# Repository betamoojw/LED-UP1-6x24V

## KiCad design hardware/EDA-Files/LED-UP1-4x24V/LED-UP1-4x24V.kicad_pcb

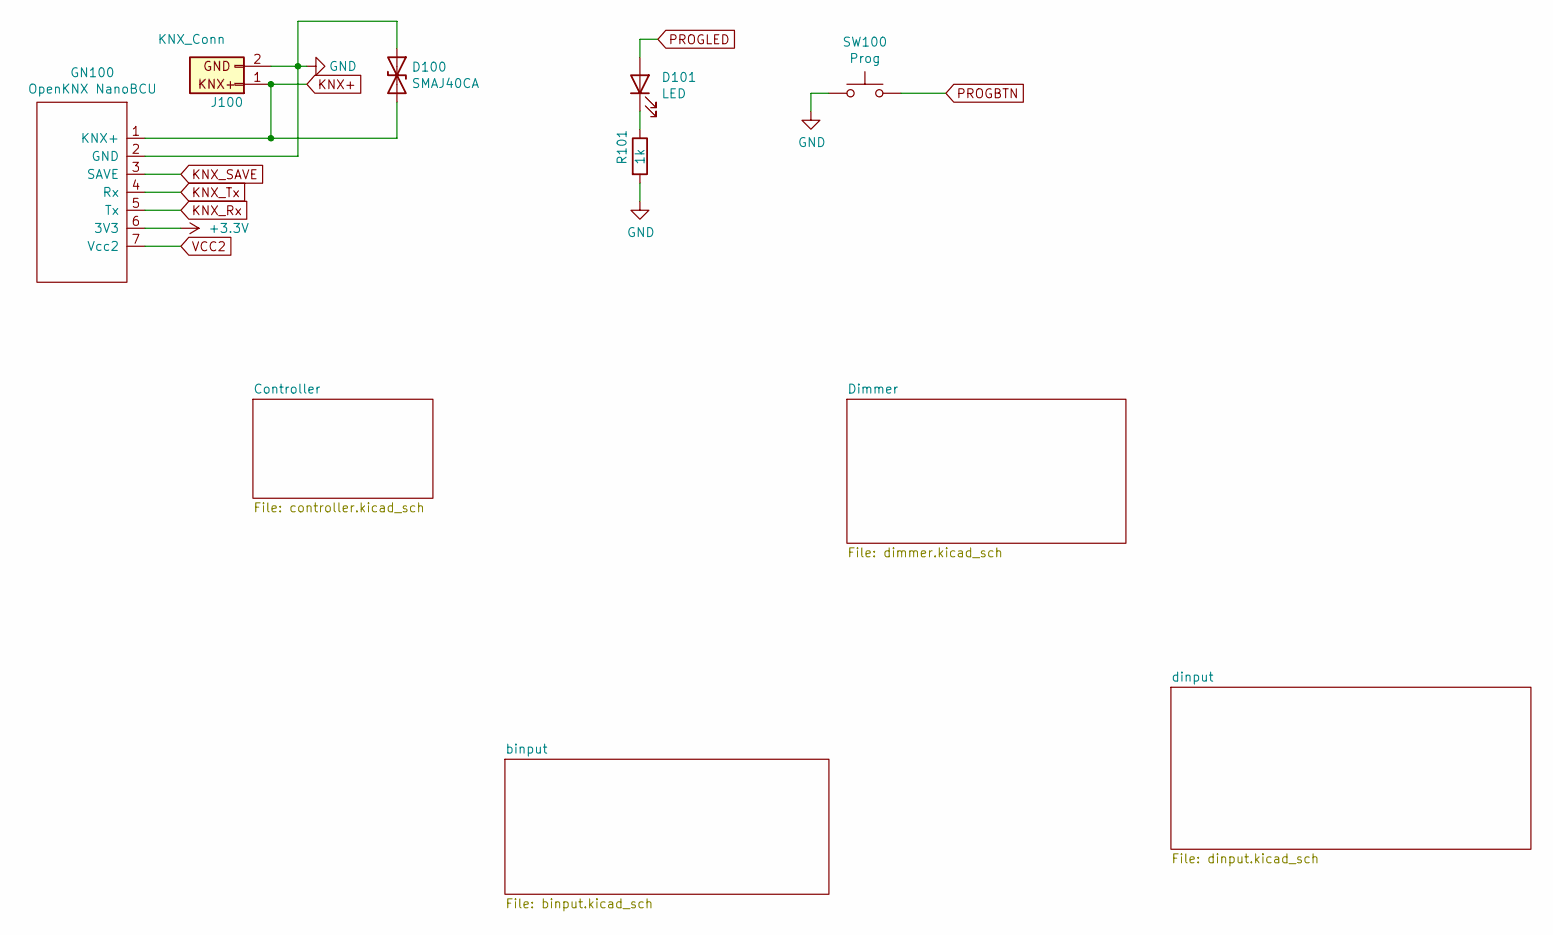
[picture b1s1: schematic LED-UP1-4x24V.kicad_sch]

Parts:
D100: SMAJ40CA; D_SMA; LCSC C113970
D101: LED; LED_0603_1608Metric; LCSC C2286
GN100: OpenKNX NanoBCU; NanoBCU_PinHeader_SMD_low_profile; LCSC C5160790
J100: KNX_Conn; KNX_Connector
R101: 1k; R_0402_1005Metric; LCSC C11702
SW100: Prog; C455282_SW-SMD_4P-L4.2-W3.3-P2.15-LS5.1; LCSC C455282

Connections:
+3.3V: GN100.6 (3V3); also elsewhere on the board
GND: D100.1 (A1), GN100.2 (GND), J100.2, R101.2, SW100.1; also elsewhere on the board
KNX+: D100.2 (A2), GN100.1 (KNX+), J100.1
KNX_Rx: GN100.5 (Tx); also elsewhere on the board
KNX_SAVE: GN100.3 (SAVE); also elsewhere on the board
KNX_Tx: GN100.4 (Rx); also elsewhere on the board
unnamed: D101.1 (K), R101.1
PROGBTN: SW100.2; also elsewhere on the board
PROGLED: D101.2 (A); also elsewhere on the board
VCC2: GN100.7 (Vcc2)

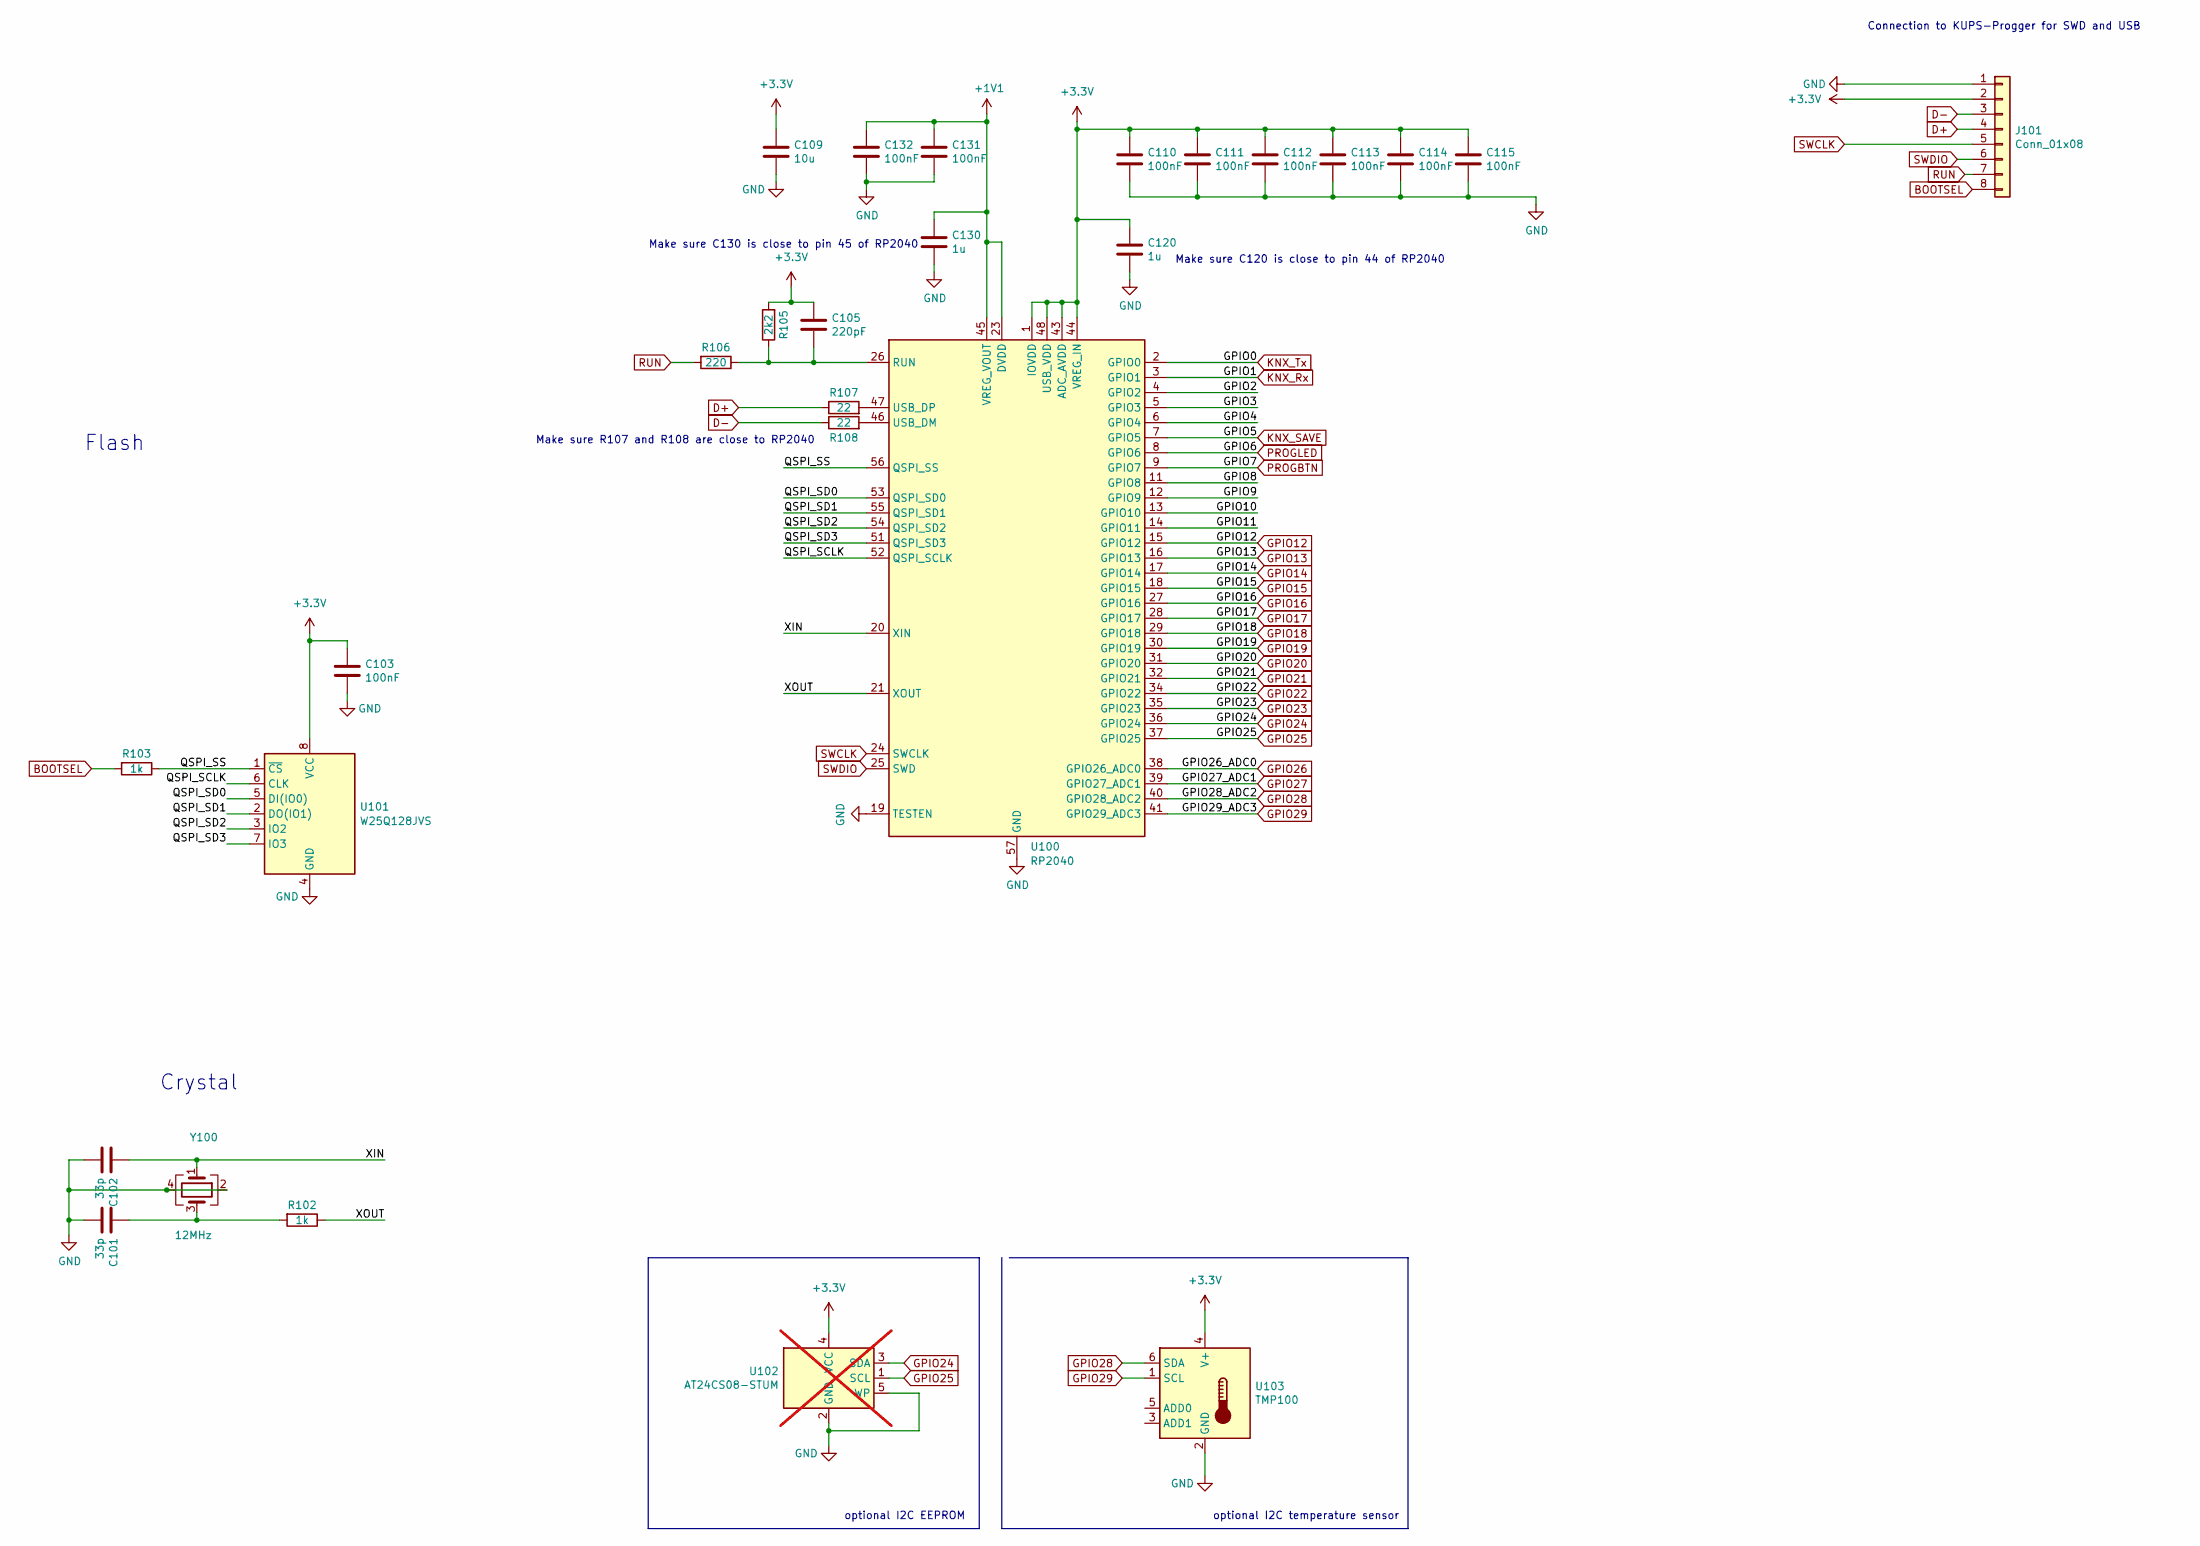
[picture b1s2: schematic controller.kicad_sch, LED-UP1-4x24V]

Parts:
C101, C102: 33p; C_0402_1005Metric; LCSC C1562
C103, C110, C111, C112, C113, C114, C115, C131, C132: 100nF; C_0402_1005Metric; LCSC C307331
C105: 220pF; C_0402_1005Metric; LCSC C1530
C109: 10u; C_0805_2012Metric; LCSC C15850
C120, C130: 1u; C_0402_1005Metric; LCSC C52923
J101: Conn_01x08; PinHeader_1x08_P1.27mm_Vertical; LCSC C2337
R102, R103: 1k; C_0402_1005Metric; LCSC C11702
R105: 2k2; C_0402_1005Metric; LCSC C25879
R106: 220; R_0402_1005Metric; LCSC C25091
R107, R108: 22; C_0402_1005Metric; LCSC C25092
U100: RP2040; QFN-56-1EP_7x7mm_P0.4mm_EP3.2x3.2mm; LCSC C2040
U101: W25Q128JVS; SOIC-8_5.275x5.275mm_P1.27mm; LCSC C97521
U102: AT24CS08-STUM; SOT-23-5; LCSC C232875; not fitted
U103: TMP100; SOT-23-6; LCSC C31810
Y100: 12MHz; Crystal_SMD_3225-4Pin_3.2x2.5mm; LCSC C9002

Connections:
+1V1: C130.1, C131.1, C132.1, U100.23 (DVDD), U100.45 (VREG_VOUT), U100.50 (DVDD)
+3.3V: C103.1, C105.1, C109.1, C110.1, C111.1, C112.1, C113.1, C114.1, C115.1, C120.1, J101.2, R105.2, U100.1 (IOVDD), U100.10 (IOVDD), U100.22 (IOVDD), U100.33 (IOVDD), U100.42 (IOVDD), U100.43 (ADC_AVDD), U100.44 (VREG_IN), U100.48 (USB_VDD), U100.49 (IOVDD), U101.8 (VCC), U102.4 (VCC), U103.4 (V+); also elsewhere on the board
/Controller/GPIO2: U100.4 (GPIO2)
/Controller/GPIO3: U100.5 (GPIO3)
/Controller/GPIO4: U100.6 (GPIO4)
/Controller/GPIO8: U100.11 (GPIO8)
/Controller/GPIO9: U100.12 (GPIO9)
/Controller/GPIO10: U100.13 (GPIO10)
/Controller/GPIO11: U100.14 (GPIO11)
/Controller/QSPI_SCLK: U100.52 (QSPI_SCLK), U101.6 (CLK)
/Controller/QSPI_SD0: U100.53 (QSPI_SD0), U101.5 (DI(IO0))
/Controller/QSPI_SD1: U100.55 (QSPI_SD1), U101.2 (DO(IO1))
/Controller/QSPI_SD2: U100.54 (QSPI_SD2), U101.3 (IO2)
/Controller/QSPI_SD3: U100.51 (QSPI_SD3), U101.7 (IO3)
/Controller/QSPI_SS: R103.1, U100.56 (QSPI_SS), U101.1 (~CS)
/Controller/XIN: C102.1, U100.20 (XIN), Y100.1
/Controller/XOUT: R102.1, U100.21 (XOUT)
BOOTSEL: J101.8, R103.2
D+: J101.4, R107.1
D-: J101.3, R108.1
GND: C101.2, C102.2, C103.2, C109.2, C110.2, C111.2, C112.2, C113.2, C114.2, C115.2, C120.2, C130.2, C131.2, C132.2, J101.1, U100.19 (TESTEN), U100.57 (GND), U101.4 (GND), U102.2 (GND), U102.5 (WP), U103.2 (GND), Y100.2, Y100.4; also elsewhere on the board
GPIO12: U100.15 (GPIO12)
GPIO13: U100.16 (GPIO13); also elsewhere on the board
GPIO14: U100.17 (GPIO14); also elsewhere on the board
GPIO15: U100.18 (GPIO15); also elsewhere on the board
GPIO16: U100.27 (GPIO16)
GPIO17: U100.28 (GPIO17); also elsewhere on the board
GPIO18: U100.29 (GPIO18); also elsewhere on the board
GPIO19: U100.30 (GPIO19)
GPIO20: U100.31 (GPIO20); also elsewhere on the board
GPIO21: U100.32 (GPIO21)
GPIO22: U100.34 (GPIO22); also elsewhere on the board
GPIO23: U100.35 (GPIO23)
GPIO24: U100.36 (GPIO24), U102.3 (SDA); also elsewhere on the board
GPIO25: U100.37 (GPIO25), U102.1 (SCL)
GPIO26: U100.38 (GPIO26_ADC0); also elsewhere on the board
GPIO27: U100.39 (GPIO27_ADC1); also elsewhere on the board
GPIO28: U100.40 (GPIO28_ADC2), U103.6 (SDA)
GPIO29: U100.41 (GPIO29_ADC3), U103.1 (SCL)
KNX_Rx: U100.3 (GPIO1); also elsewhere on the board
KNX_SAVE: U100.7 (GPIO5); also elsewhere on the board
KNX_Tx: U100.2 (GPIO0); also elsewhere on the board
unnamed: C101.1, R102.2, Y100.3
unnamed: C105.2, R105.1, R106.1, U100.26 (RUN)
unnamed: R108.2, U100.46 (USB_DM)
unnamed: R107.2, U100.47 (USB_DP)
PROGBTN: U100.9 (GPIO7); also elsewhere on the board
PROGLED: U100.8 (GPIO6); also elsewhere on the board
RUN: J101.7, R106.2
SWCLK: J101.5, U100.24 (SWCLK)
SWDIO: J101.6, U100.25 (SWD)

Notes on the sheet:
Make sure C130 is close to pin 45 of RP2040
optional I2C temperature sensor
Flash
optional I2C EEPROM
Crystal
Connection to KUPS-Progger for SWD and USB
Make sure C120 is close to pin 44 of RP2040
Make sure R107 and R108 are close to RP2040

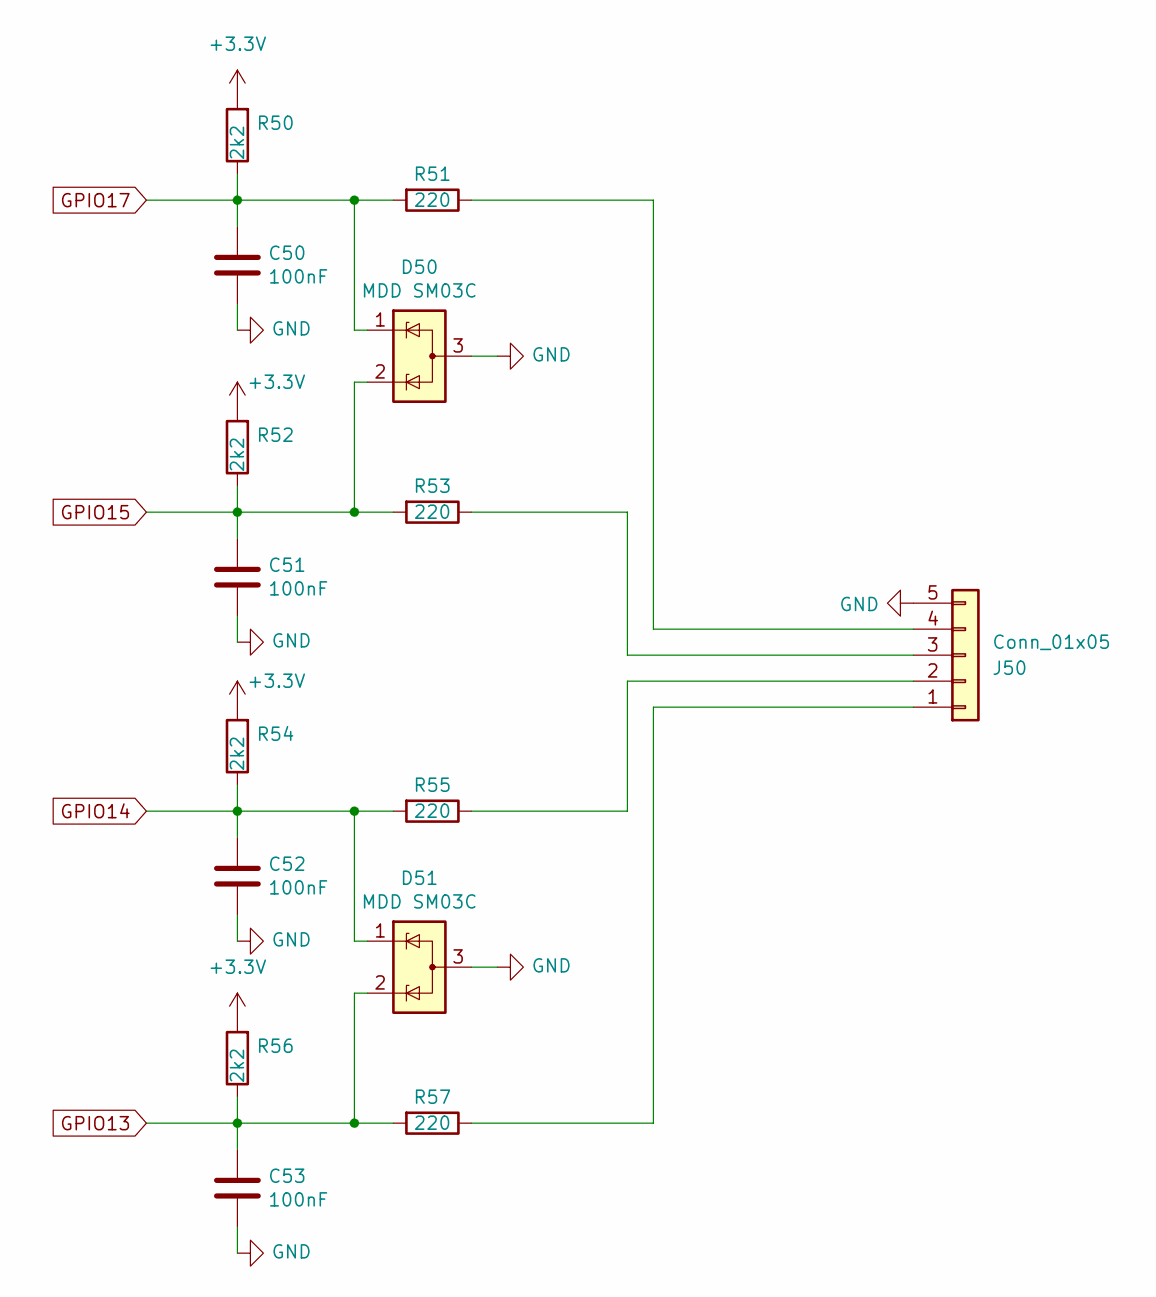
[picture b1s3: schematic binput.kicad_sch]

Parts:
C50, C51, C52, C53: 100nF; C_0402_1005Metric; LCSC C307331
D50, D51: MDD SM03C; SOT-23; LCSC C502553
J50: Conn_01x05; Cixi_Kefa_KF128-2.54-5p; LCSC C474923
R50, R52, R54, R56: 2k2; R_0402_1005Metric; LCSC C25879
R51, R53, R55, R57: 220; R_0402_1005Metric; LCSC C25091

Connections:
+3.3V: R50.2, R52.2, R54.2, R56.2; also elsewhere on the board
GND: C50.2, C51.2, C52.2, C53.2, D50.3 (A), D51.3 (A), J50.5; also elsewhere on the board
GPIO13: C53.1, D51.2 (K), R56.1, R57.2; also elsewhere on the board
GPIO14: C52.1, D51.1 (K), R54.1, R55.2; also elsewhere on the board
GPIO15: C51.1, D50.2 (K), R52.1, R53.2; also elsewhere on the board
GPIO17: C50.1, D50.1 (K), R50.1, R51.2; also elsewhere on the board
unnamed: J50.1, R57.1
unnamed: J50.2, R55.1
unnamed: J50.3, R53.1
unnamed: J50.4, R51.1

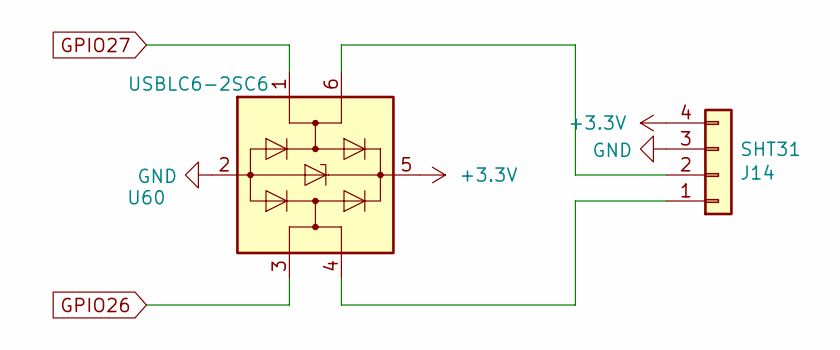
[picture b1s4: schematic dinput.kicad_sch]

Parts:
J14: SHT31; Cixi_Kefa_KF128-2.54-4p; LCSC C474922
U60: USBLC6-2SC6; SOT-23-6; LCSC C2827654

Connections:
+3.3V: U60.5 (VBUS); also elsewhere on the board
GND: U60.2 (GND); also elsewhere on the board
GPIO26: U60.3 (I/O2); also elsewhere on the board
GPIO27: U60.1 (I/O1); also elsewhere on the board
unnamed 55: U60.4 (I/O2); also elsewhere on the board
unnamed 56: U60.6 (I/O1); also elsewhere on the board

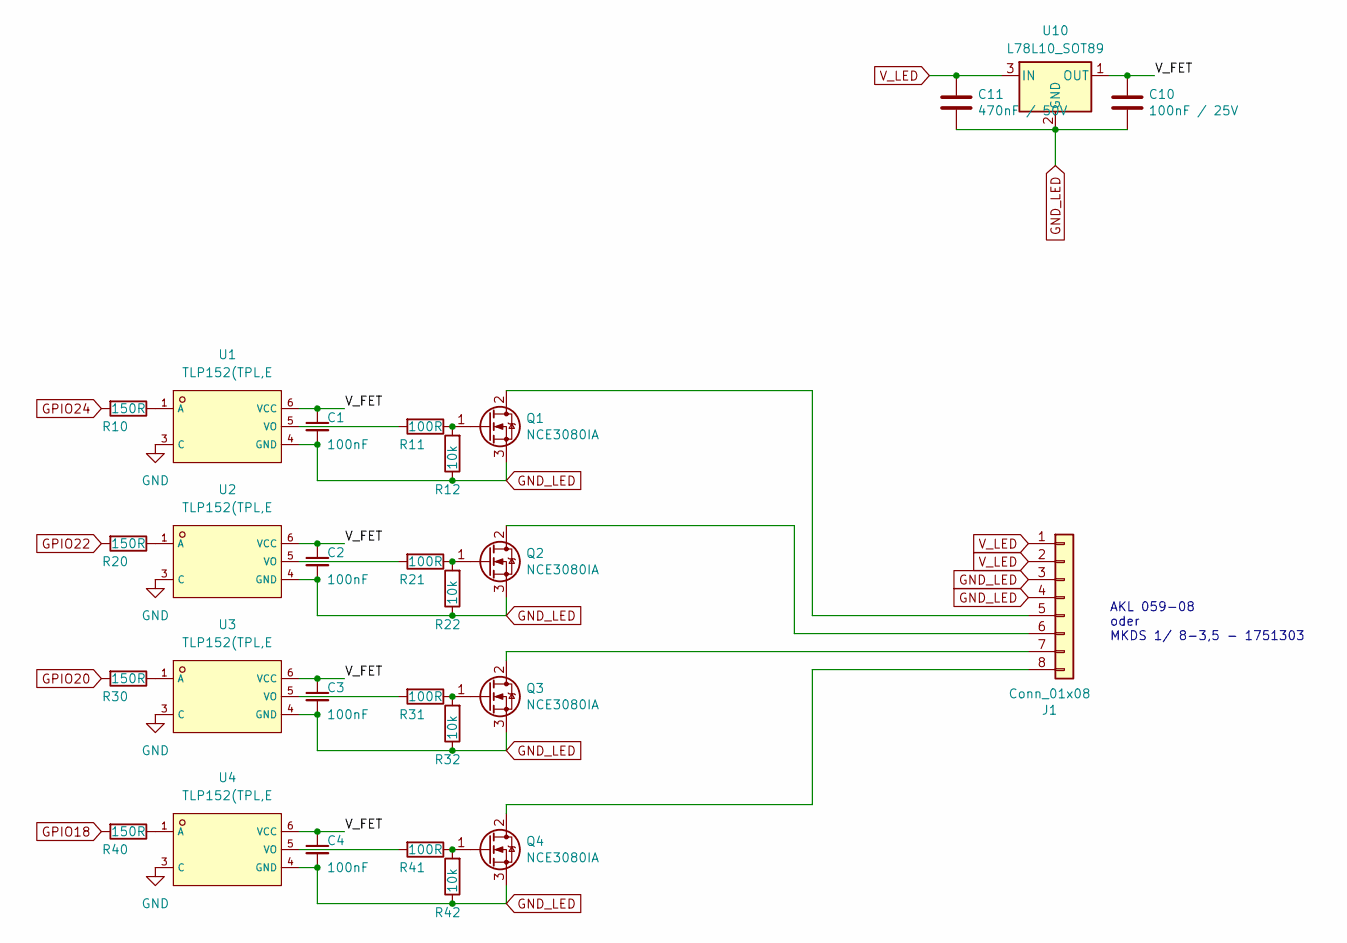
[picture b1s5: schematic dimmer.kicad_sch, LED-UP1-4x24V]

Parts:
C1, C2, C3, C4: 100nF; C_0402_1005Metric; LCSC C307331
C10: 100nF / 25V; C_0805_2012Metric; LCSC C49678
C11: 470nF / 50V; C_0805_2012Metric; LCSC C13967
J1: Conn_01x08; PhoenixContact_MKDS_1,5_8-G-3.5_1x08_P3.5mm_Horizontal; LCSC C5184954
Q1, Q2, Q3, Q4: NCE3080IA; TO-251-3_Vertical_lowprofile; LCSC C326369
R10, R20, R30, R40: 150R; R_0603_1608Metric; LCSC C22808
R11, R21, R31, R41: 100R; R_0402_1005Metric; LCSC C25076
R12, R22, R32, R42: 10k; R_0402_1005Metric; LCSC C25744
U1, U2, U3, U4: TLP152(TPL,E; OPTO-SMD_SO-5_L4.6-W3.7-P1.27-BR; LCSC C150122
U10: L78L10_SOT89; SOT-89-3; LCSC C75500

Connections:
/Dimmer/V_FET: C1.1, C2.1, C3.1, C4.1, C10.1, U1.6 (VCC), U2.6 (VCC), U3.6 (VCC), U4.6 (VCC), U10.1 (OUT)
GND: U1.3 (C), U2.3 (C), U3.3 (C), U4.3 (C); also elsewhere on the board
GND_LED: C1.2, C2.2, C3.2, C4.2, C10.2, C11.2, J1.3, J1.4, Q1.3 (S), Q2.3 (S), Q3.3 (S), Q4.3 (S), R12.1, R22.1, R32.1, R42.1, U1.4 (GND), U2.4 (GND), U3.4 (GND), U4.4 (GND), U10.2 (GND)
GPIO18: R40.2; also elsewhere on the board
GPIO20: R30.2; also elsewhere on the board
GPIO22: R20.2; also elsewhere on the board
GPIO24: R10.2; also elsewhere on the board
unnamed: J1.5, Q1.2 (D)
unnamed: J1.6, Q2.2 (D)
unnamed: J1.7, Q3.2 (D)
unnamed: J1.8, Q4.2 (D)
unnamed: Q1.1 (G), R11.1, R12.2
unnamed: Q2.1 (G), R21.1, R22.2
unnamed: Q3.1 (G), R31.1, R32.2
unnamed: Q4.1 (G), R41.1, R42.2
unnamed: R10.1, U1.1 (A)
unnamed: R11.2, U1.5 (VO)
unnamed: R20.1, U2.1 (A)
unnamed: R21.2, U2.5 (VO)
unnamed: R30.1, U3.1 (A)
unnamed: R31.2, U3.5 (VO)
unnamed: R40.1, U4.1 (A)
unnamed: R41.2, U4.5 (VO)
V_LED: C11.1, J1.1, J1.2, U10.3 (IN)

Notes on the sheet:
AKL 059-08 oder MKDS 1/ 8-3,5 - 1751303

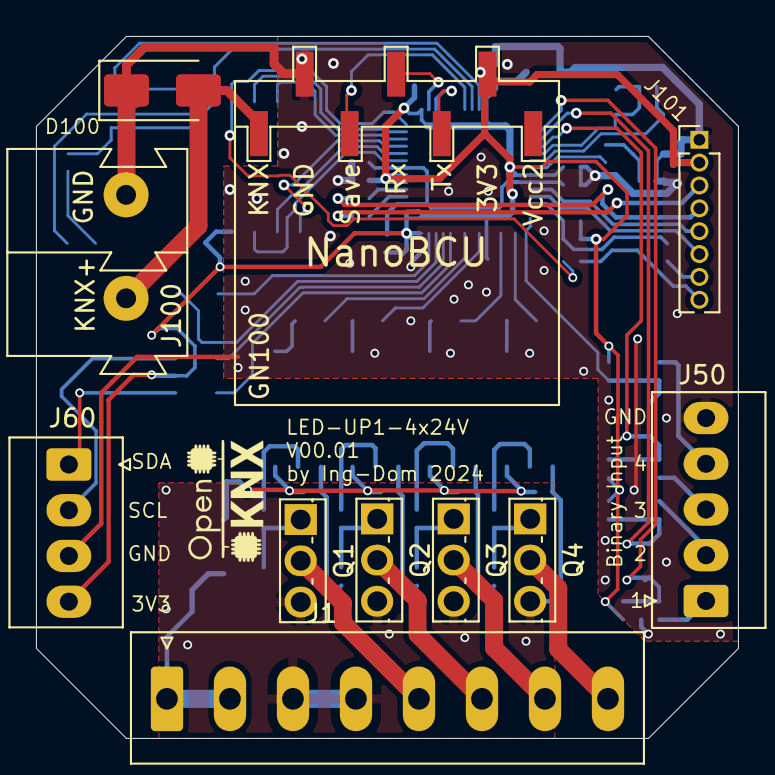
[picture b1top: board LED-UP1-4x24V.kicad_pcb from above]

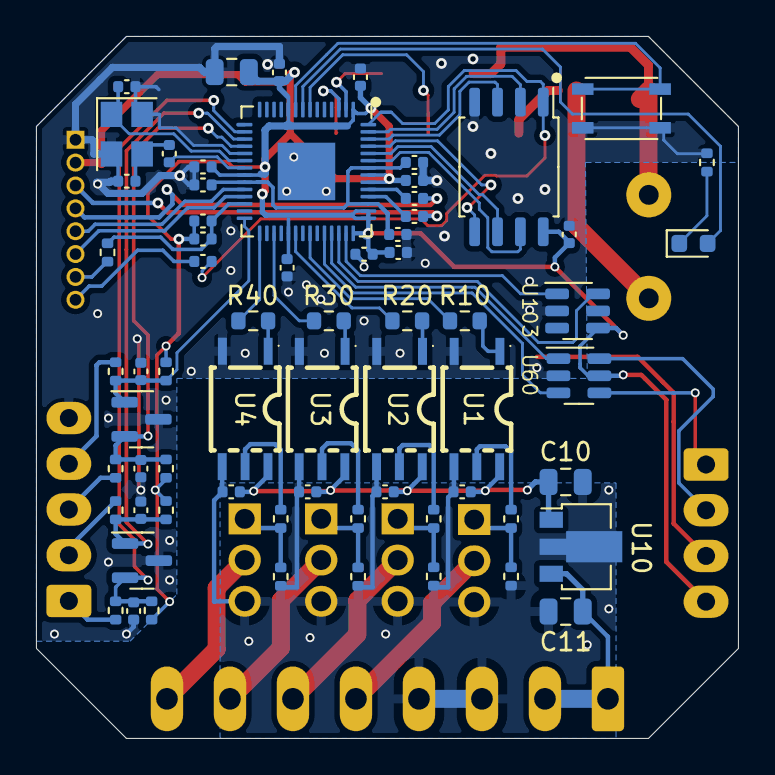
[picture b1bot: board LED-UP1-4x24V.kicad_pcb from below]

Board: 2 copper layers, 39.0 x 39.0 mm, 77 parts (66 on the bottom side), 65 nets.

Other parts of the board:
J60: SHT31; Cixi_Kefa_KF128-2.54-4p

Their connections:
+3.3V: J60.4; also elsewhere on the board
GND: J60.3; also elsewhere on the board
unnamed 55: J60.1; also elsewhere on the board
unnamed 56: J60.2; also elsewhere on the board

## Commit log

2024-03-28 New LED-UP1-4x24V
